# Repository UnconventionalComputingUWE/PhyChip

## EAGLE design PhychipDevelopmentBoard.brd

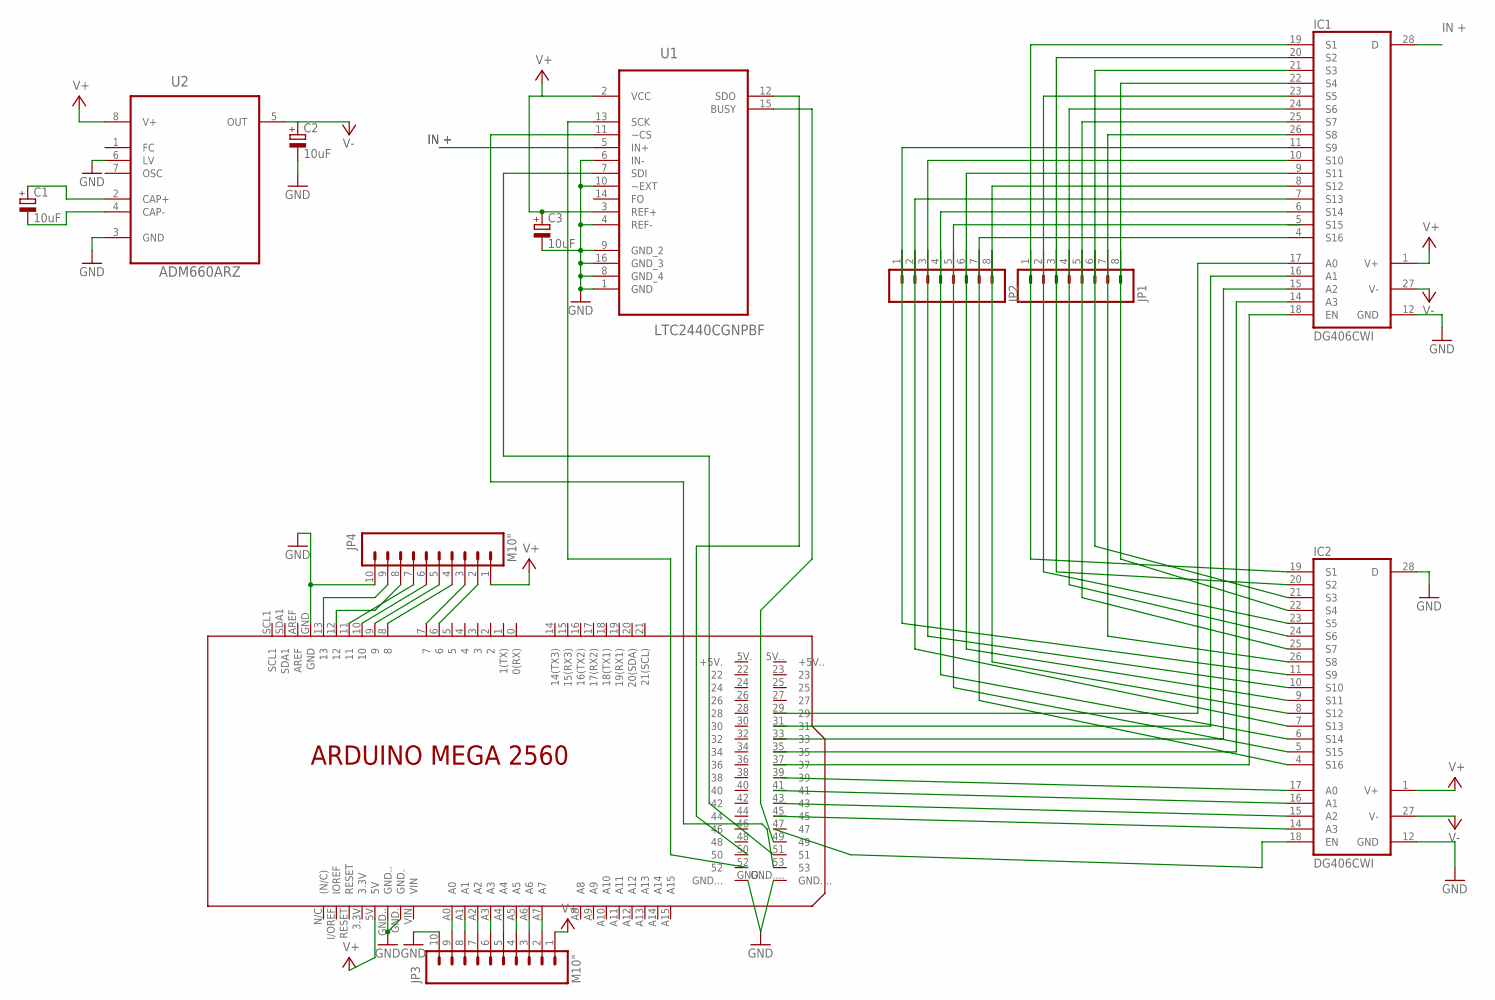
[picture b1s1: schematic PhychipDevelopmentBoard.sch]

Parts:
C1, C2, C3: 10uF; 153CLV-0505
IC1, IC2: DG406CWI; SO28L
JP1, JP2: M08; 1X08
JP3, JP4: M10"; 1X10
PCB1: ARDUINO_MEGA2560
U1: LTC2440CGNPBF; SOP63P600X175-16N
U2: ADM660ARZ; SOIC127P600X175-8N

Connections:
GND: C2.-, C3.-, IC1.12 (GND), IC2.12 (GND), IC2.28 (D), JP3.10, JP4.10, PCB1.GND, PCB1.GND., PCB1.GND.., PCB1.GND..., PCB1.GND...., U1.1 (GND), U1.4 (REF-), U1.6 (IN-), U1.8 (GND_4), U1.9 (GND_2), U1.10 (~EXT), U1.16 (GND_3), U2.3 (GND), U2.6 (LV)
IN+: IC1.28 (D), U1.5 (IN+)
unnamed: C1.+, U2.2 (CAP+)
unnamed: C1.-, U2.4 (CAP-)
unnamed: PCB1.52, U1.13 (SCK)
unnamed: PCB1.50, U1.12 (SDO)
unnamed: PCB1.51, U1.7 (SDI)
unnamed: PCB1.49, U1.15 (BUSY)
unnamed: PCB1.53, U1.11 (~CS)
unnamed: IC2.18 (EN), PCB1.47
unnamed: IC2.14 (A3), PCB1.45
unnamed: IC2.15 (A2), PCB1.43
unnamed: IC2.16 (A1), PCB1.41
unnamed: IC2.17 (A0), PCB1.39
unnamed: IC1.18 (EN), PCB1.37
unnamed: IC1.14 (A3), PCB1.35
unnamed: IC1.15 (A2), PCB1.33
unnamed: IC1.16 (A1), PCB1.31
unnamed: IC1.17 (A0), PCB1.29
unnamed: IC1.19 (S1), IC2.19 (S1), JP1.1
unnamed: IC1.20 (S2), IC2.20 (S2), JP1.3
unnamed: IC1.21 (S3), IC2.21 (S3), JP1.6
unnamed: IC1.22 (S4), IC2.22 (S4), JP1.8
unnamed: IC1.23 (S5), IC2.23 (S5), JP1.2
unnamed: IC1.24 (S6), IC2.24 (S6), JP1.4
unnamed: IC1.25 (S7), IC2.25 (S7), JP1.5
unnamed: IC1.26 (S8), IC2.26 (S8), JP1.7
unnamed: IC1.11 (S9), IC2.11 (S9), JP2.1
unnamed: IC1.10 (S10), IC2.10 (S10), JP2.3
unnamed: IC1.9 (S11), IC2.9 (S11), JP2.6
unnamed: IC1.8 (S12), IC2.8 (S12), JP2.8
unnamed: JP3.9, PCB1.A0
unnamed: JP3.8, PCB1.A1
unnamed: JP3.7, PCB1.A2
unnamed: JP3.6, PCB1.A3
unnamed: JP3.5, PCB1.A4
unnamed: JP3.4, PCB1.A5
unnamed: JP3.3, PCB1.A6
unnamed: JP3.2, PCB1.A7
unnamed: IC1.7 (S13), IC2.7 (S13), JP2.2
unnamed: JP4.9, PCB1.13
unnamed: IC1.6 (S14), IC2.6 (S14), JP2.4
unnamed: IC2.5 (S15), JP2.5
unnamed: IC1.4 (S16), IC2.4 (S16), JP2.7
unnamed: JP4.8, PCB1.12
unnamed: JP4.7, PCB1.11
unnamed: JP4.6, PCB1.10
unnamed: JP4.5, PCB1.9
unnamed: JP4.4, PCB1.8
unnamed: JP4.3, PCB1.7
unnamed: JP4.2, PCB1.6
V+: C3.+, IC1.1 (V+), IC2.1 (V+), JP3.1, JP4.1, PCB1.5V, U1.2 (VCC), U1.3 (REF+), U2.8 (V+)
V-: C2.+, IC1.27 (V-), IC2.27 (V-), U2.5 (OUT)

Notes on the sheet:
IN +

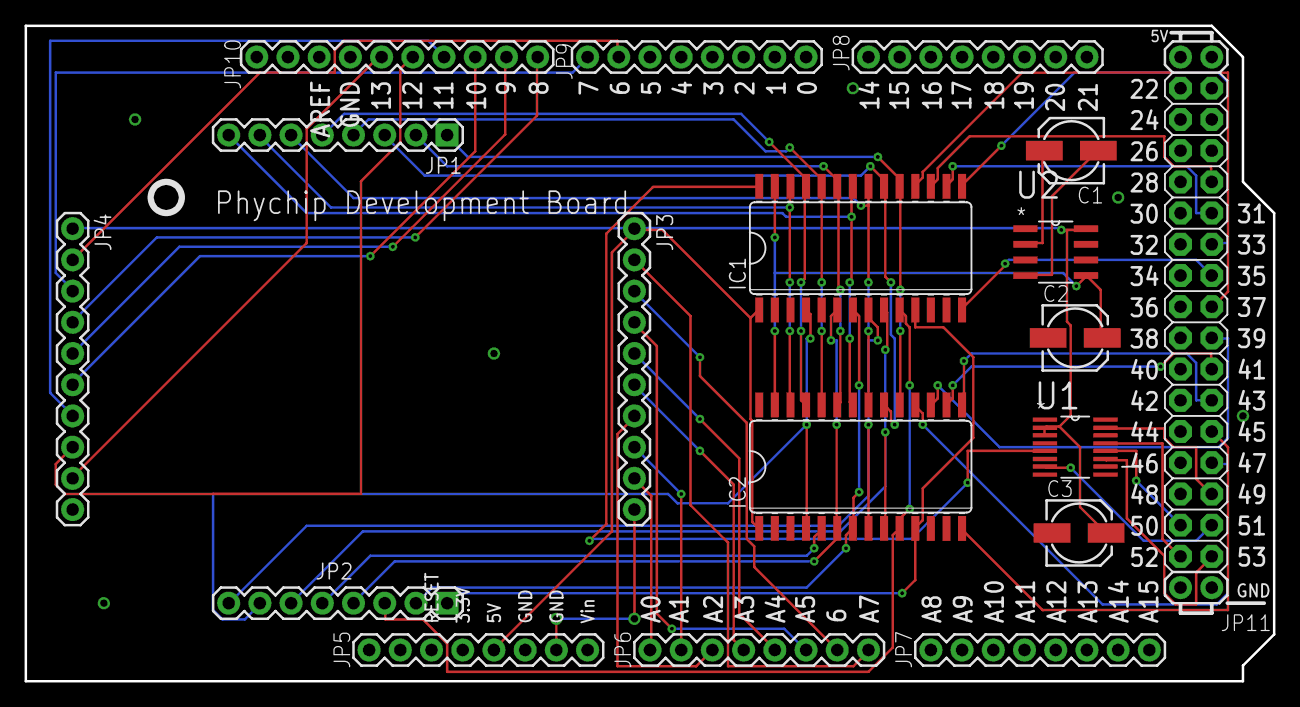
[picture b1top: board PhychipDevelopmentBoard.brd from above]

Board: 2 copper layers, 101.6 x 53.3 mm, 12 parts (0 on the bottom side), 53 nets.

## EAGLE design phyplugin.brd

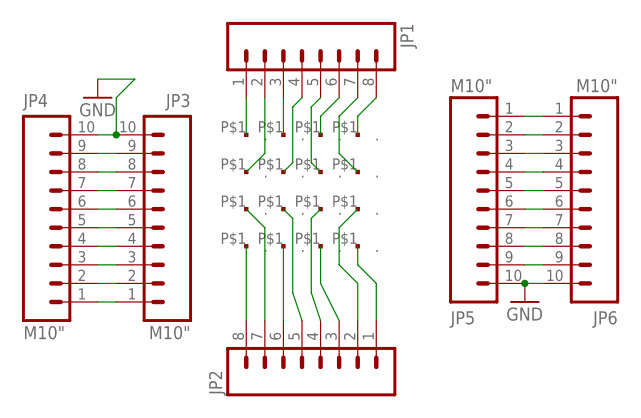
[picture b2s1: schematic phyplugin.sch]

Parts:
JP1, JP2: M08; 1X08
JP3, JP4, JP5, JP6: M10"; 1X10
U$1, U$2, U$3, U$4, U$5, U$6, U$7, U$8, U$9, U$10, U$11, U$12, U$13, U$14, U$15, U$16: MEAPAD; MEAPAD1MM

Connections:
GND: JP3.10, JP4.10, JP5.10, JP6.10
unnamed: JP1.4, U$6.P$1
unnamed: JP1.5, U$7.P$1
unnamed: JP1.3, U$2.P$1
unnamed: JP1.6, U$3.P$1
unnamed: JP1.2, U$5.P$1
unnamed: JP1.1, U$1.P$1
unnamed: JP1.7, U$8.P$1
unnamed: JP1.8, U$4.P$1
unnamed: JP2.5, U$10.P$1
unnamed: JP2.4, U$11.P$1
unnamed: JP2.6, U$14.P$1
unnamed: JP2.3, U$15.P$1
unnamed: JP2.7, U$9.P$1
unnamed: JP2.2, U$12.P$1
unnamed: JP2.1, U$16.P$1
unnamed: JP2.8, U$13.P$1
unnamed: JP5.1, JP6.1
unnamed: JP3.1, JP4.1
unnamed: JP3.2, JP4.2
unnamed: JP3.3, JP4.3
unnamed: JP3.4, JP4.4
unnamed: JP3.5, JP4.5
unnamed: JP3.6, JP4.6
unnamed: JP3.7, JP4.7
unnamed: JP3.8, JP4.8
unnamed: JP3.9, JP4.9
unnamed: JP5.2, JP6.2
unnamed: JP5.3, JP6.3
unnamed: JP5.4, JP6.4
unnamed: JP5.5, JP6.5
unnamed: JP5.6, JP6.6
unnamed: JP5.7, JP6.7
unnamed: JP5.8, JP6.8
unnamed: JP5.9, JP6.9

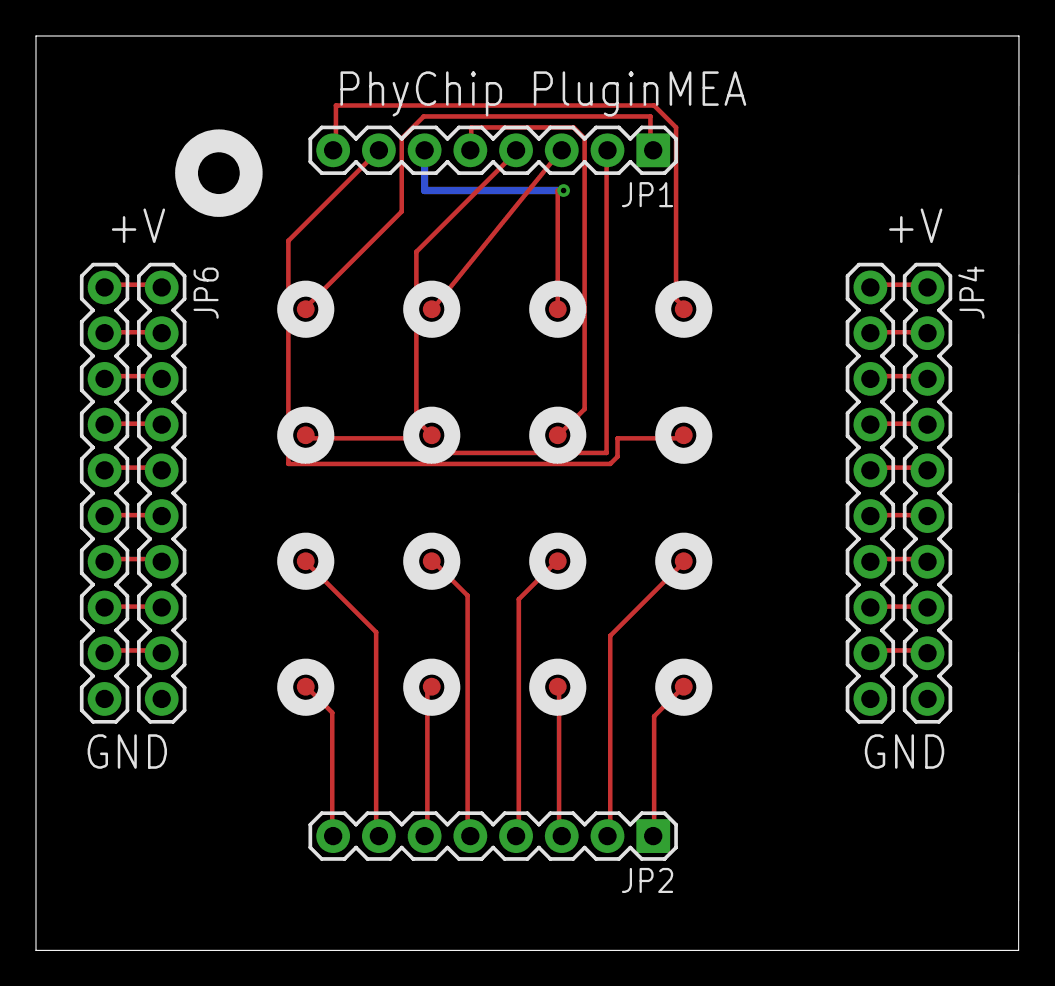
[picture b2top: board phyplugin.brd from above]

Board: 2 copper layers, 54.6 x 50.8 mm, 22 parts (0 on the bottom side), 35 nets.

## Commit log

2017-04-04 Create Bill_Of_Materials
2017-04-04 Rename phychipDevelopmentBoardV0.9.brd to Phychip Development Board.brd
2017-04-04 Rename phychipDevelopmentBoardV0.9.sch to Phychip Development Board.sch
2017-04-04 Create Arduino Pin map
2017-04-05 Rename phychipDevelopmentBoardV0.9.brd to PhychipDevelopmentBoard.brd
2017-04-05 Rename phychipDevelopmentBoardV0.9.sch to PhychipDevelopmentBoard.sch
